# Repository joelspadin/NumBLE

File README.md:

# NumBLE Wireless Numpad

NumBLE is a Bluetooth numpad with 3D printed case, based on the
[Nordic nNRF52840 SoC](https://www.nordicsemi.com/Products/Low-power-short-range-wireless/nRF52840).
It supports 21-key, 22-key, and 24-key layouts, and the top-left key can be
replaced with a rotary encoder. It is powered by up to an 1200 mAh Li-Po battery
with a 2-pin JST Ph connector (such as those sold by [Adafruit](https://www.adafruit.com/category/574))
and supports USB-C for charging and wired operation.

This is a DIY project and is not sold anywhere.
[Check the wiki](https://github.com/joelspadin/NumBLE/wiki) for instructions on
how to build one.

## Hardware

The PCB is hand-solderable, though it uses many small parts which are difficult
to solder by hand. It supports an optional fuel gauge IC, which provides more
accurate battery status but requires reflow soldering. The [pcb folder](pcb)
contains a [KiCad](https://www.kicad.org/) project (requires KiCad 5.99 nightly
builds).

The [case folder](case) contains the design files for the case and plate. The
case is 3D printed in two parts, and the plate is attached to the bottom with
four bolts into threaded inserts. The top attaches to the bottom with magnets
glued into both halves.

Removing the top of the case exposes power and reset switches. The power switch
only affects the numpad when in wireless mode. When wired, it is always powered
and will charge the battery regardless of the position of the power switch.

## Software

NumBLE runs [ZMK Firmware](https://zmkfirmware.dev/). The [config folder](config)
holds the source files for the firmware. To customize the keymap, create a new
repo using the [ZMK Config Template](https://github.com/zmkfirmware/unified-zmk-config-template),
then edit the `config/west.yml` file to include this repo as an additional module.

Next, edit the `build.yaml` file and add

```ymal
include:
  - board: numble
  - board: numble
    shield: settings_reset
```

Commit and push the changes to GitHub, and it will automatically build the new
firmware for you. Check the "Actions" tab above for the build results.

The bootloader is built with [my fork of Adafruit's nRF52 bootloader](https://github.com/joelspadin/Adafruit_nRF52_Bootloader).

There are other firmwares that can run on an nRF52, and I will be happy to
answer questions on setting them up for NumBLE, but I do not plan to personally
support them.

The bootloader included in the releases does not contain the SoftDevice, as
Zephyr does not need it. If you'd like to run firmware that requires the
SoftDevice, you can either compile the bootloader yourself, or let me know and I
can include multiple versions of the bootloader in releases.

## Status

Some parts of the hardware have not yet been fully tested.

| Feature                           | Status                                                  |
| --------------------------------- | ------------------------------------------------------- |
| 21-key layout                     | Working                                                 |
| 22-key layout                     | Untested                                                |
| 24-key layout                     | Untested                                                |
| Encoder                           | Untested                                                |
| Battery reporting with fuel gauge | Partially tested, requires driver updates in Zephyr 2.6 |
| Voltage-based battery reporting   | Working                                                 |

## More Renders

## Credits

The case was designed with [Fusion 360](https://www.autodesk.com/products/fusion-360).
Renders use the [Interior HDRI free pack](https://www.maximeroz.com/hdri-free-pack)
by Maxime Roz.

The KiCAD project uses symbols and footprints from:

- [ai03-2725/MX_Alps_Hybrid](https://github.com/ai03-2725/MX_Alps_Hybrid)
- [ai03-2725/Type-C.pretty](https://github.com/ai03-2725/Type-C.pretty)
- [joric/nrfmicro](https://github.com/joric/nrfmicro)

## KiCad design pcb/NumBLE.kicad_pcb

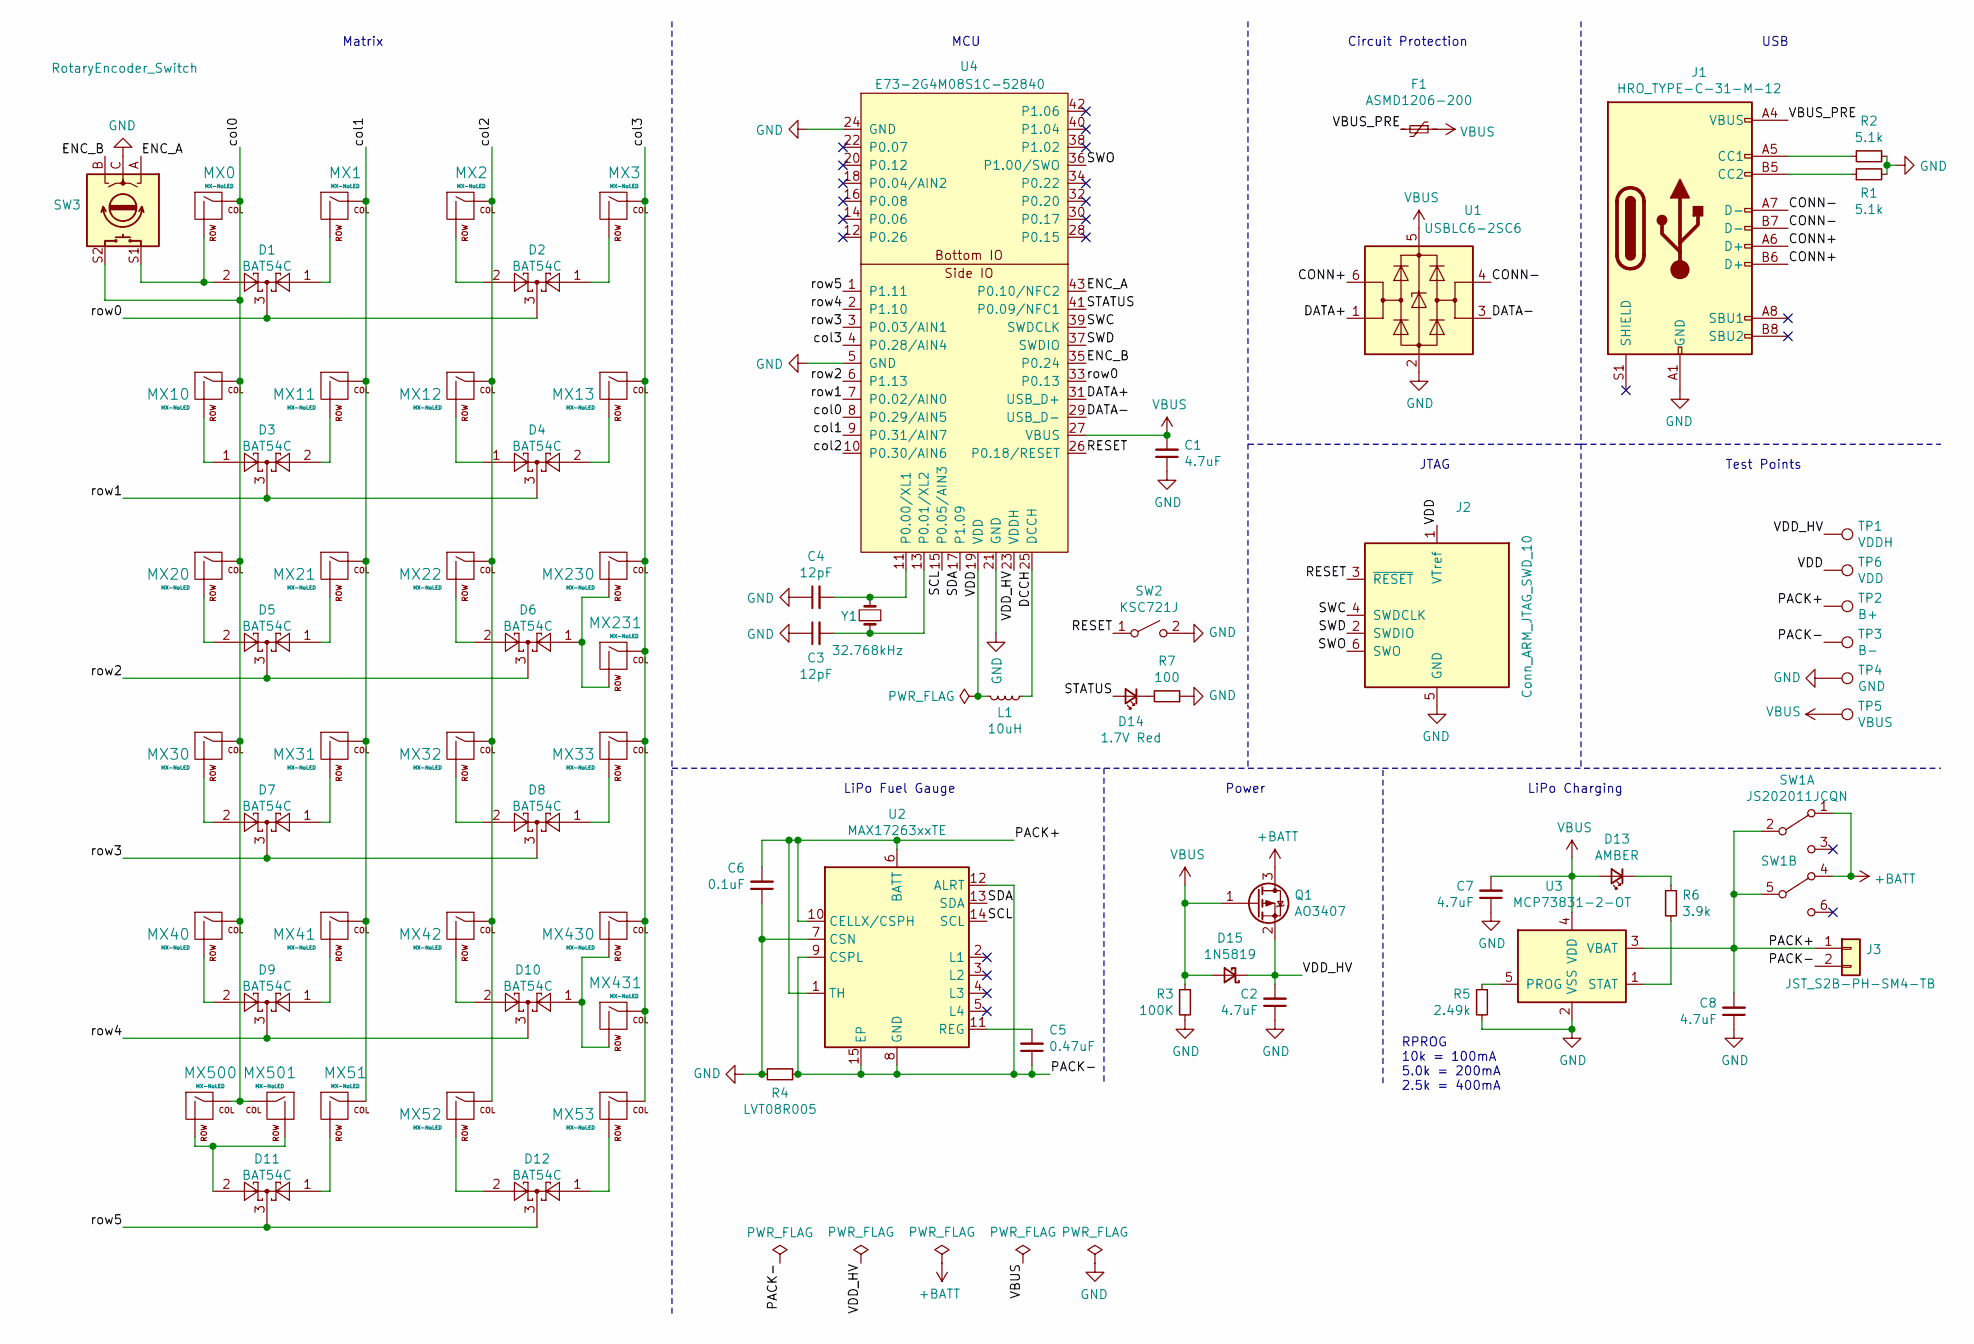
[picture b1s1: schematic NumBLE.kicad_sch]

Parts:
C1, C2, C7, C8: 4.7uF; C_0603_1608Metric_Pad1.08x0.95mm_HandSolder
C3, C4: 12pF; C_0603_1608Metric_Pad1.08x0.95mm_HandSolder
C5: 0.47uF; C_0603_1608Metric_Pad1.08x0.95mm_HandSolder
C6: 0.1uF; C_0603_1608Metric_Pad1.08x0.95mm_HandSolder
D1, D2, D3, D4, D5, D6, D7, D8, D9, D10, D11, D12: BAT54C; SOT-23
D13: AMBER; LED_0603_1608Metric
D14: 1.7V Red; LED_0603_1608Metric
D15: 1N5819; D_SOD-323_HandSoldering
F1: ASMD1206-200; Fuse_0805_2012Metric_Pad1.15x1.40mm_HandSolder
J1: HRO_TYPE-C-31-M-12; USB_C_Receptacle_HRO_TYPE-C-31-M-12
J2: Conn_ARM_JTAG_SWD_10; Tag-Connect_TC2030-IDC-NL_2x03_P1.27mm_Vertical
J3: JST_S2B-PH-SM4-TB; JST_PH_S2B-PH-SM4-TB_1x02-1MP_P2.00mm_Horizontal
L1: 10uH; L_0603_1608Metric_Pad1.05x0.95mm_HandSolder
MX0, MX1, MX2, MX3, MX10, MX11, MX12, MX13, MX20, MX21, MX22, MX30, MX31, MX32, MX33, MX40, MX41, MX42, MX52, MX53, MX230, MX430: MX-NoLED; MXOnly-1U-NoLED
MX51: MX-NoLED; MXOnly-1U-2U-Right
MX231, MX431: MX-NoLED; MXOnly-2U-ReversedStabilizers-NoLED
MX500: MX-NoLED; MXOnly-1U-2U-Left
MX501: MX-NoLED; MXOnly-1U-2U-Center-ReversedStabilizers
Q1: AO3407; SOT-23
R1, R2: 5.1k; R_0603_1608Metric_Pad0.98x0.95mm_HandSolder
R3: 100K; R_0603_1608Metric_Pad0.98x0.95mm_HandSolder
R4: LVT08R005; LVT08Rxxx0xER
R5: 2.49k; R_0603_1608Metric_Pad0.98x0.95mm_HandSolder
R6: 3.9k; R_0603_1608Metric_Pad0.98x0.95mm_HandSolder
R7: 100; R_0603_1608Metric_Pad0.98x0.95mm_HandSolder
SW1: JS202011JCQN; SW_DPDT_CK_JS202011JCQN
SW2: KSC721J; SW_Push_1P1T_NO_CK_KSC7xxJ
SW3: RotaryEncoder_Switch; RotaryEncoder_Alps_EC11E-Switch_Vertical_H20mm
TP1: VDDH; TestPoint_Pad_D1.5mm
TP2: B+; TestPoint_Pad_D1.5mm
TP3: B-; TestPoint_Pad_D1.5mm
TP4: GND; TestPoint_Pad_D1.5mm
TP5: VBUS; TestPoint_Pad_D1.5mm
TP6: VDD; TestPoint_Pad_D1.5mm
U1: USBLC6-2SC6; SOT-23-6
U2: MAX17263xxTE; DFN-14-1EP_3x3mm_P0.4mm_EP1.78x2.35mm
U3: MCP73831-2-OT; SOT-23-5
U4: E73-2G4M08S1C-52840
Y1: 32.768kHz; Crystal_SMD_3215-2Pin_3.2x1.5mm

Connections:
+BATT: Q1.3 (D), SW1.1 (A), SW1.4 (A)
/CONN+: J1.A6 (D+), J1.B6 (D+), U1.6 (I/O1)
/CONN-: J1.A7 (D-), J1.B7 (D-), U1.4 (I/O2)
/DATA+: U1.1 (I/O1), U4.31 (USB_D+)
/DATA-: U1.3 (I/O2), U4.29 (USB_D-)
/DCCH: L1.1, U4.25 (DCCH)
/ENC_A: SW3.A, U4.43 (P0.10/NFC2)
/ENC_B: SW3.B, U4.35 (P0.24)
/PACK+: C6.2, C8.2, J3.1, SW1.2 (B), SW1.5 (B), TP2.1, U2.1 (TH), U2.6 (BATT), U2.10 (CELLX/CSPH), U3.3 (VBAT)
/PACK-: C5.1, J3.2, R4.1, TP3.1, U2.8 (GND), U2.9 (CSPL), U2.12 (ALRT), U2.15 (EP)
/RESET: J2.3 (~RESET~), SW2.1 (A), U4.26 (P0.18/RESET)
/SCL: U2.14 (SCL), U4.15 (P0.05/AIN3)
/SDA: U2.13 (SDA), U4.17 (P1.09)
/STATUS: D14.2 (A), U4.41 (P0.09/NFC1)
/SWC: J2.4 (SWDCLK), U4.39 (SWDCLK)
/SWD: J2.2 (SWDIO), U4.37 (SWDIO)
/SWO: J2.6 (SWO), U4.36 (P1.00/SWO)
/VBUS_PRE: F1.2, J1.A4 (VBUS), J1.A9 (VBUS), J1.B4 (VBUS), J1.B9 (VBUS)
/VDD: J2.1 (VTref), L1.2, TP6.1, U4.19 (VDD)
/VDD_HV: C2.2, D15.1 (K), Q1.2 (S), TP1.1, U4.23 (VDDH)
/col0: MX0.1 (COL), MX10.1 (COL), MX20.1 (COL), MX30.1 (COL), MX40.1 (COL), MX500.1 (COL), MX501.1 (COL), SW3.S2, U4.8 (P0.29/AIN5)
/col1: MX1.1 (COL), MX11.1 (COL), MX21.1 (COL), MX31.1 (COL), MX41.1 (COL), MX51.1 (COL), U4.9 (P0.31/AIN7)
/col2: MX2.1 (COL), MX12.1 (COL), MX22.1 (COL), MX32.1 (COL), MX42.1 (COL), MX52.1 (COL), U4.10 (P0.30/AIN6)
/col3: MX3.1 (COL), MX13.1 (COL), MX33.1 (COL), MX53.1 (COL), MX230.1 (COL), MX231.1 (COL), MX430.1 (COL), MX431.1 (COL), U4.4 (P0.28/AIN4)
/row0: D1.3, D2.3, U4.33 (P0.13)
/row1: D3.3, D4.3, U4.7 (P0.02/AIN0)
/row2: D5.3, D6.3, U4.6 (P1.13)
/row3: D7.3, D8.3, U4.3 (P0.03/AIN1)
/row4: D9.3, D10.3, U4.2 (P1.10)
/row5: D11.3, D12.3, U4.1 (P1.11)
GND: C1.1, C2.1, C3.1, C4.1, C6.1, C7.1, C8.1, J1.A1 (GND), J1.A12 (GND), J1.B1 (GND), J1.B12 (GND), J2.5 (GND), R1.2, R2.1, R3.2, R4.2, R5.2, R7.1, SW2.2 (B), SW3.C, TP4.1, U1.2 (GND), U2.7 (CSN), U3.2 (VSS), U4.5 (GND), U4.21 (GND), U4.24 (GND)
unnamed: C3.2, U4.13 (P0.01/XL2), Y1.1
unnamed: C4.2, U4.11 (P0.00/XL1), Y1.2
unnamed: C5.2, U2.11 (REG)
unnamed: D1.1, MX1.2 (ROW)
unnamed: D1.2, MX0.2 (ROW), SW3.S1
unnamed: D2.1, MX3.2 (ROW)
unnamed: D2.2, MX2.2 (ROW)
unnamed: D3.1, MX10.2 (ROW)
unnamed: D3.2, MX11.2 (ROW)
unnamed: D4.1, MX12.2 (ROW)
unnamed: D4.2, MX13.2 (ROW)
unnamed: D5.1, MX21.2 (ROW)
unnamed: D5.2, MX20.2 (ROW)
unnamed: D6.1, MX230.2 (ROW), MX231.2 (ROW)
unnamed: D6.2, MX22.2 (ROW)
unnamed: D7.1, MX31.2 (ROW)
unnamed: D7.2, MX30.2 (ROW)
unnamed: D8.1, MX33.2 (ROW)
unnamed: D8.2, MX32.2 (ROW)
unnamed: D9.1, MX41.2 (ROW)
unnamed: D9.2, MX40.2 (ROW)
unnamed: D10.1, MX430.2 (ROW), MX431.2 (ROW)
unnamed: D10.2, MX42.2 (ROW)
unnamed: D11.1, MX51.2 (ROW)
unnamed: D11.2, MX500.2 (ROW), MX501.2 (ROW)
unnamed: D12.1, MX53.2 (ROW)
unnamed: D12.2, MX52.2 (ROW)
unnamed: D13.1 (K), R6.1
unnamed: D14.1 (K), R7.2
unnamed: J1.A5 (CC1), R2.2
unnamed: J1.B5 (CC2), R1.1
unnamed: R5.1, U3.5 (PROG)
unnamed: R6.2, U3.1 (STAT)
VBUS: C1.2, C7.2, D13.2 (A), D15.2 (A), F1.1, Q1.1 (G), R3.1, TP5.1, U1.5 (VBUS), U3.4 (VDD), U4.27 (VBUS)

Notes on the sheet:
Matrix
LiPo Fuel Gauge
MCU
Power
Circuit Protection
RPROG 10k = 100mA 5.0k = 200mA 2.5k = 400mA
JTAG
LiPo Charging
Test Points
USB

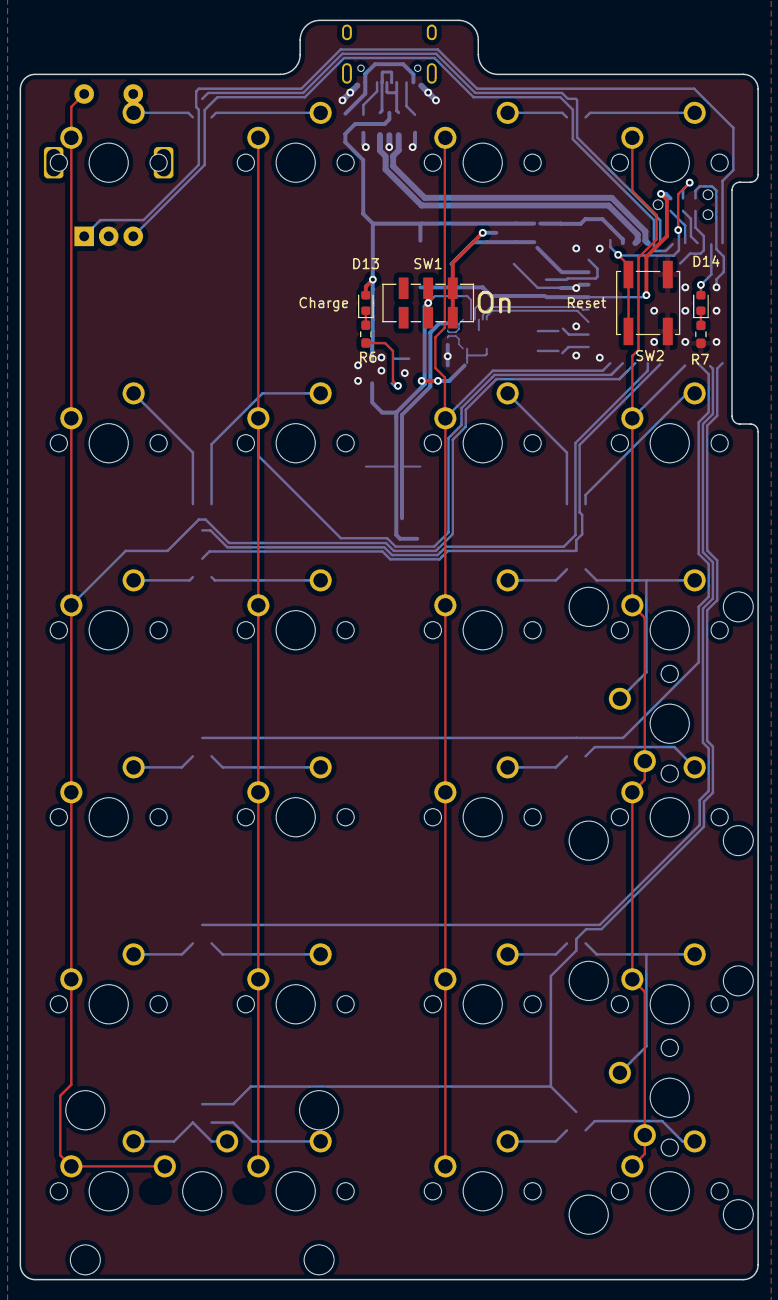
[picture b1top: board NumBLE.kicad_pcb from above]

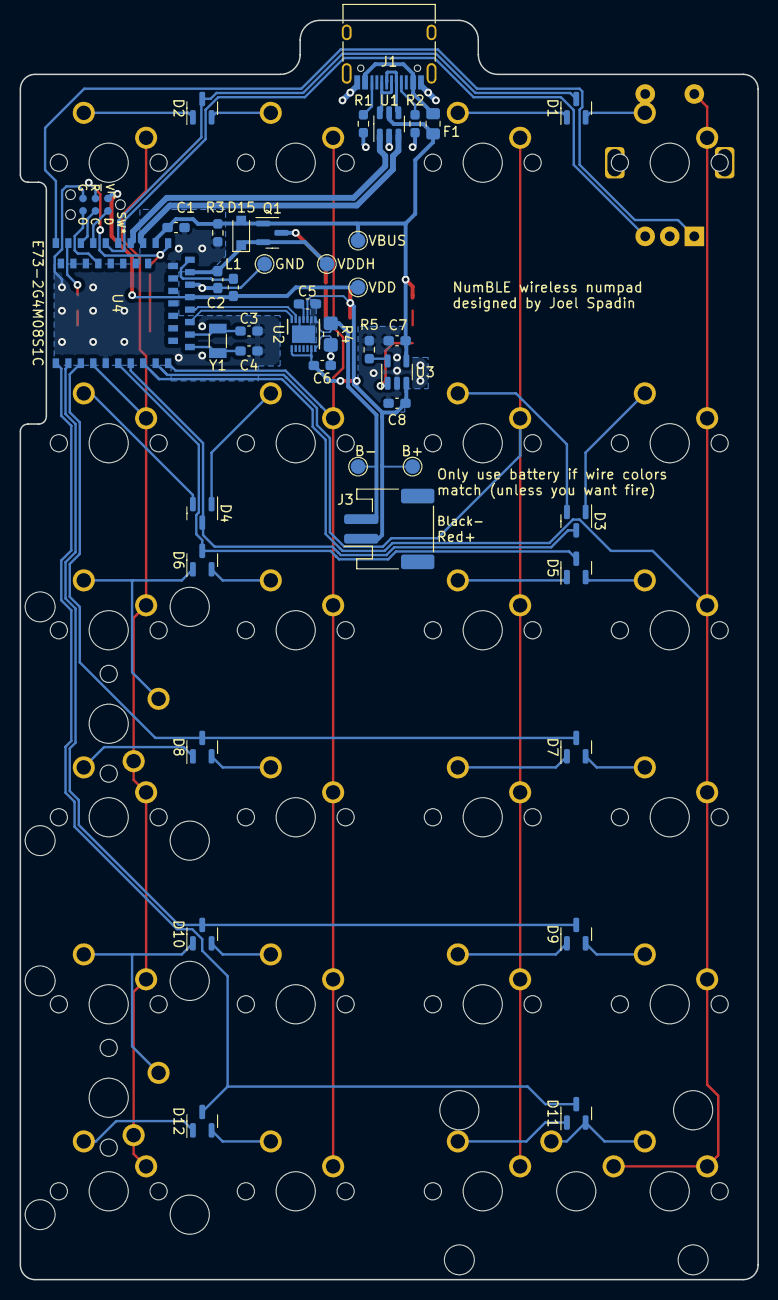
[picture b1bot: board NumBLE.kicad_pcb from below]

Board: 2 copper layers, 75.2 x 128.3 mm, 77 parts (43 on the bottom side), 65 nets.

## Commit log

2021-05-31 v1.0
2021-05-31 Move PCB files into subdirectory
2021-05-31 Add case files
2021-05-31 Fix resistor numbering
2021-06-01 Add title block to schematic
2021-06-01 Add license
2021-06-05 Add a readme
2021-06-05 Add ZMK config
2021-06-05 Improve readme
2021-06-05 Add software license
2021-06-05 Try renaming UF2 file in build artifacts
2021-06-05 Fix artifact rename
2021-06-06 Add assembly animations
2021-06-06 Only build firmware on changes to firmware files
2021-06-06 Add link to wiki in readme
2021-06-06 Add a default keyboard layout graphic
2021-06-06 Ignore VS Code workspaces
2021-07-04 Fix encoder typo
2021-07-04 Fix pull request workflow trigger
2021-07-04 Add profiles through 9 to keymap
    ZMK no longer breaks if you pick a profile larger than the max profiles.
2021-07-13 Make build.yml more configurable
2021-07-13 Can't use env vars in on.*.paths
2021-07-13 Fix typo
2021-07-17 Upgrade to Zephyr 2.5
2021-07-31 Enable VDDH battery driver by default
2022-03-14 Update for Zephyr 3.0 testing
2022-03-14 Remove settings_reset build
    settings_reset shield doesn't work with custom boards.
2022-03-14 Rebuild on changes to build.yaml
2022-04-03 Switch to stable Zephyr 3.0 branch
2022-04-03 Add a ZMK metadata file
2022-04-10 Fix battery reporting until chosen node supported
    Changed the battery sensor's label to "BATTERY" so the existing battery
    code in ZMK will pick it up while the PR to add a battery chosen node
    is still in review.
2023-10-13 Use kconfig to enable high voltage DC-DC
2024-02-14 Refactor as Zephyr module
2024-03-09 Update numble board definition
    Added support for UF2 flash runner.
    Removed deprecated labels.
    Removed unnecessary config values.
